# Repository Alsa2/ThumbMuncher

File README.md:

Stuff to add
- Perfect 1d engine model to gui
- PID I rate loss tunning

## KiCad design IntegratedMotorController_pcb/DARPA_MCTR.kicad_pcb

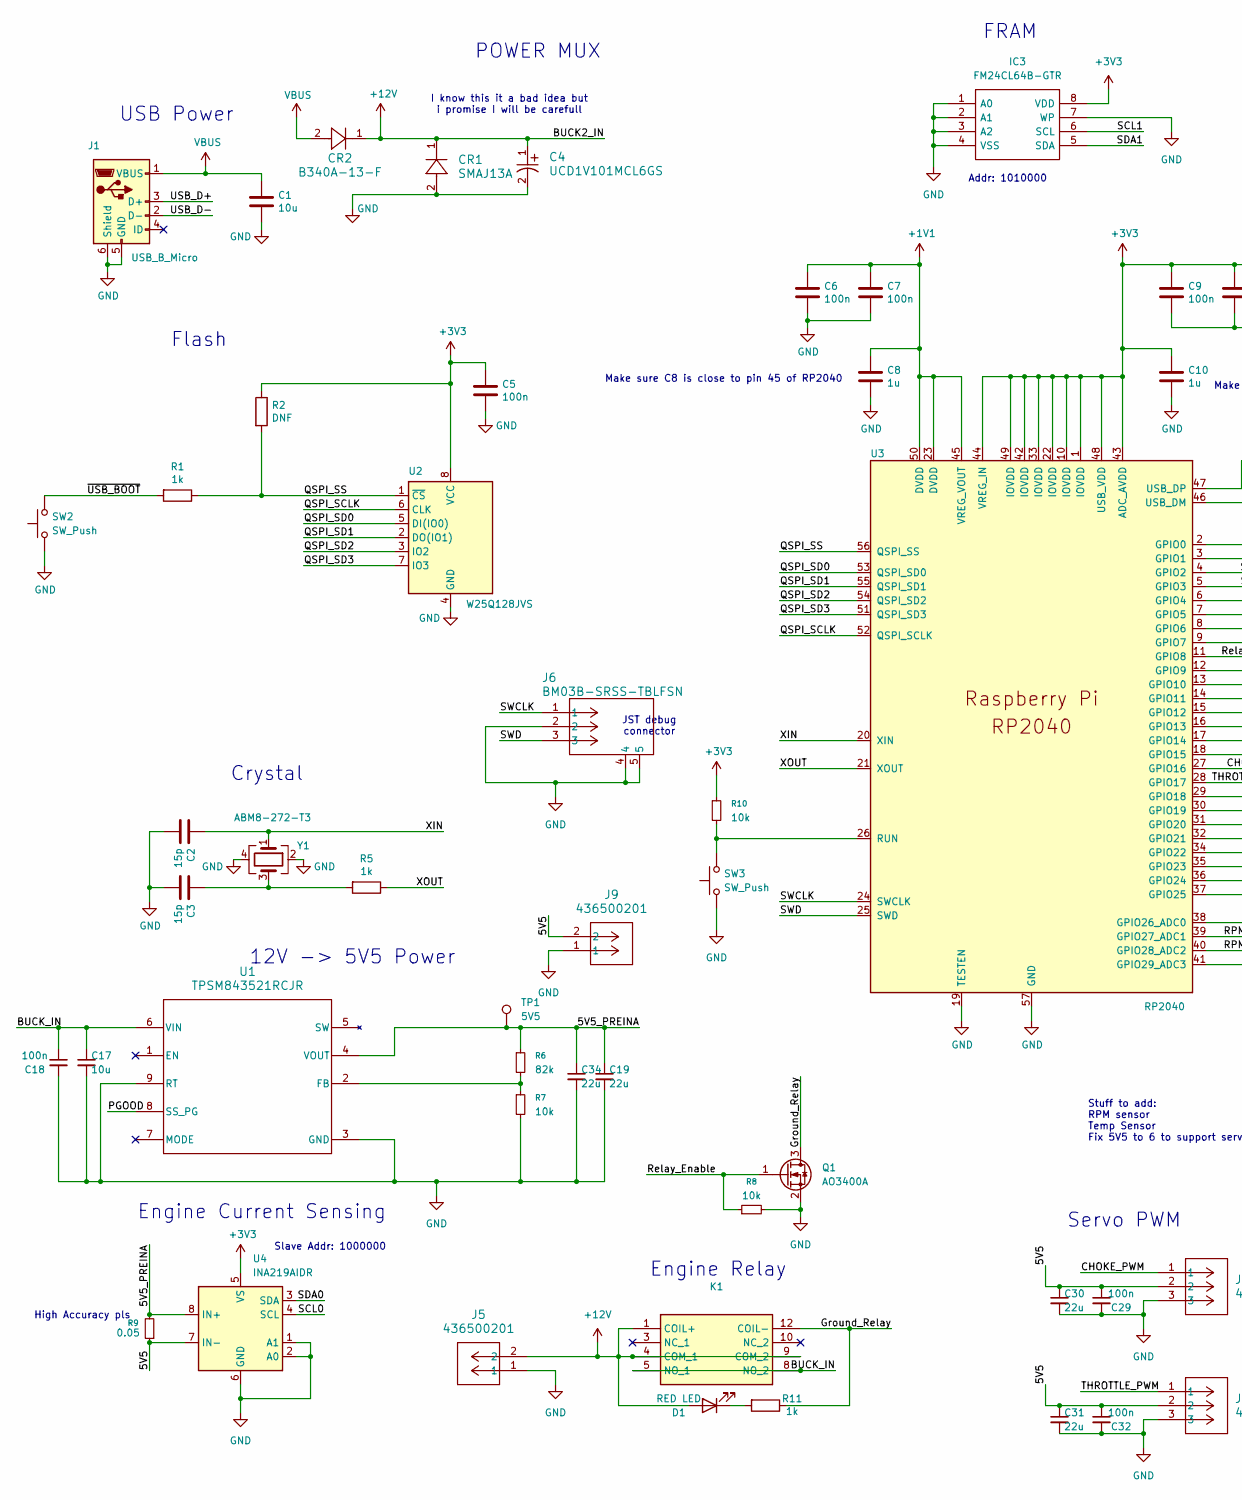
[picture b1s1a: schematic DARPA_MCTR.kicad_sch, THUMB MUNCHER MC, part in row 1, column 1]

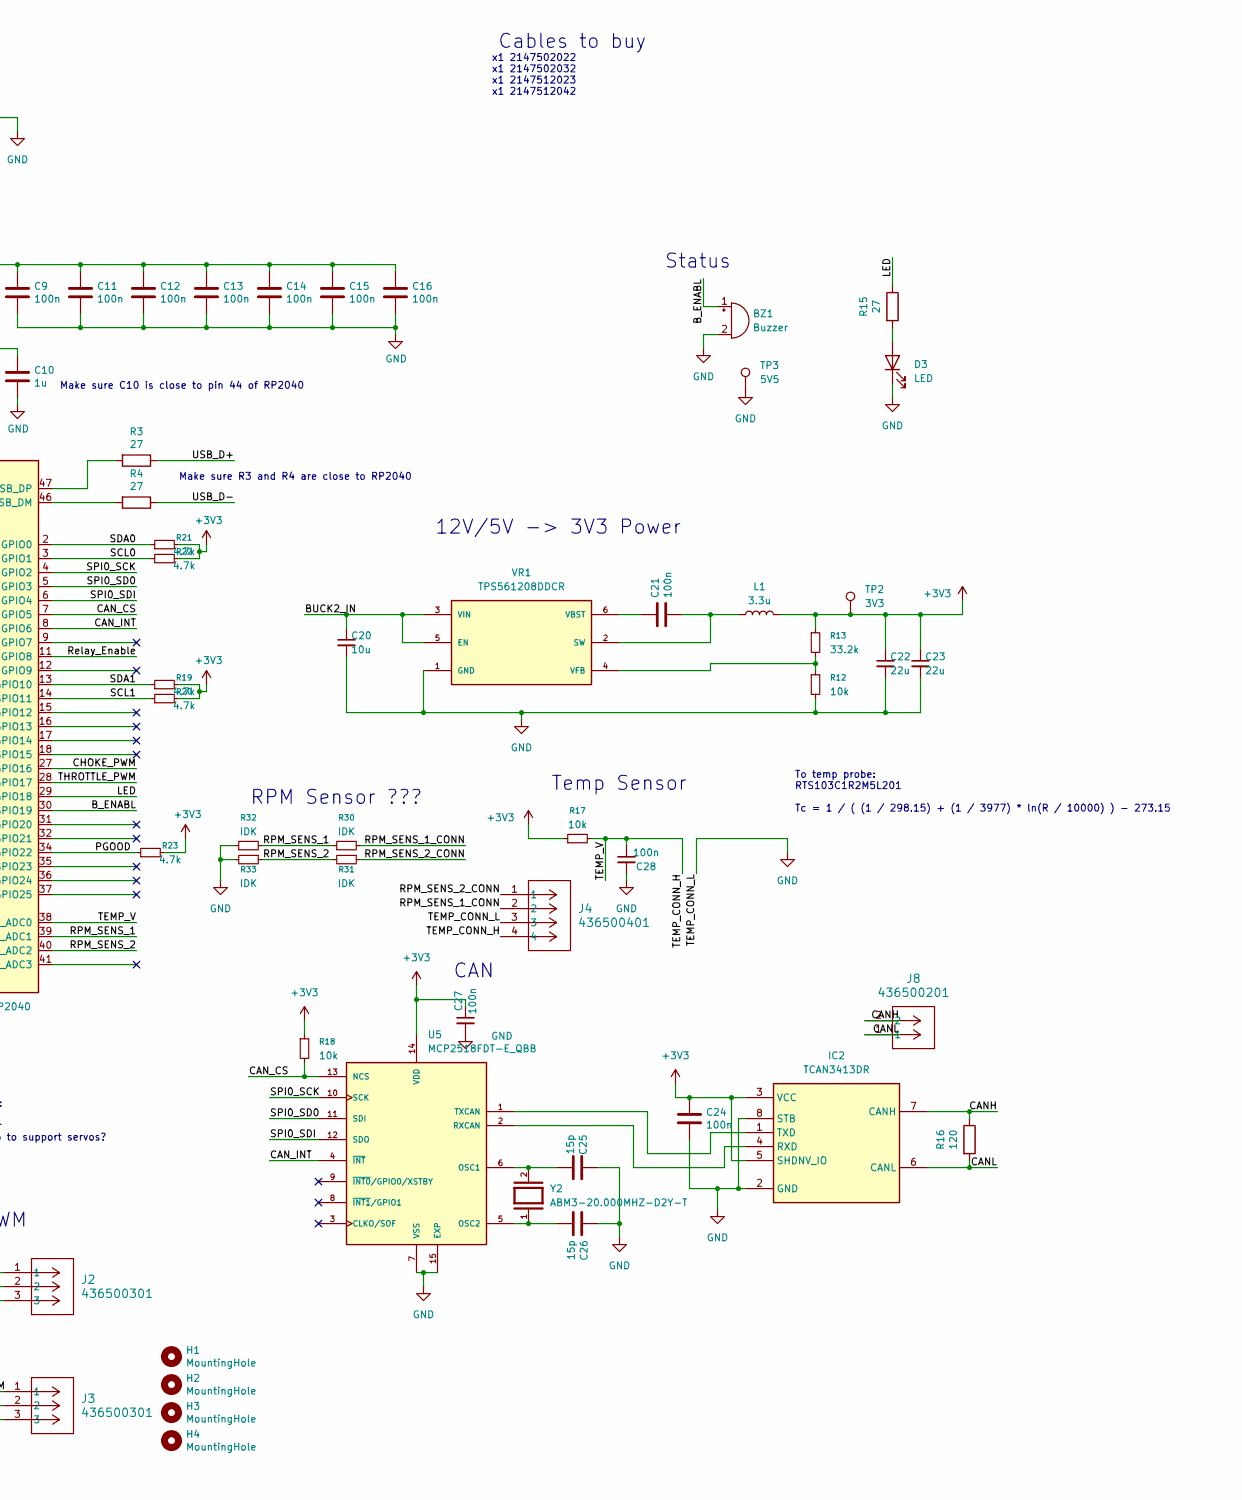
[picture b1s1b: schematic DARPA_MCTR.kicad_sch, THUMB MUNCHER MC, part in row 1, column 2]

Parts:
BZ1: Buzzer; XDCR_SMTB-1240-S-R; MPN SMTB-1240-S-R
C1, C17, C20: 10u; C_0805_2012Metric; MPN GRM21BR61C106KE15L; JLC C440198
C2, C3, C25, C26: 15p; C_0402_1005Metric; MPN GRM1555C1H150JA01D; JLC C1548
C4: UCD1V101MCL6GS; PCAP_6.3x7.7-ELECT_NCA; MPN UCD1V101MCL6GS; JLC C134220
C5, C6, C7, C9, C11, C12, C13, C14, C15, C16, C18, C21, C24, C27, C28, C29, C32: 100n; C_0402_1005Metric; MPN GRM155R71C104KA88D; JLC C71629
C8, C10: 1u; C_0402_1005Metric; MPN CL05A105KP5NNNC; JLC C14445
C19, C22, C23, C30, C31, C34: 22u; C_0805_2012Metric; MPN GRM21BR61A226ME44L; JLC C441864
CR1: SMAJ13A; SMASeries_LTF; MPN SMAJ13A; JLC C5356038
CR2: B340A-13-F; DIODE_SODB340_2P92X4P6_DIO; MPN B340A-13-F; JLC C85098
D1: RED LED; LED_0603_1608Metric; MPN QBLP601-S3; JLC C9900174479
D3: LED; LED_0603_1608Metric; MPN 150060GS75020; JLC C9900202211
H1, H2, H3, H4: MountingHole; MountingHole_2.7mm_M2.5
IC2: TCAN3413DR; SOIC127P602X173-8N; Manufacturer_Part_Number TCAN3413DR; Mouser Part Number 595-TCAN3413DR
IC3: FM24CL64B-GTR; SOIC127P602X173-8N; Manufacturer_Part_Number FM24CL64B-GTR; Mouser Part Number 877-FM24CL64B-GTR
J1: USB_B_Micro; USB_Micro-B_Amphenol_10103594-0001LF_Horizontal_modified; MPN 10103594-0001LF; JLC C428495
J2, J3: 436500301; CONN_SD-43650-001_03_MOL; MPN 0436500301
J4: 436500401; CONN_SD-43650-001_04_MOL; MPN 0436500401
J5, J8, J9: 436500201; CONN_SD-43650-001_02_MOL; MPN 0436500201
J6: BM03B-SRSS-TBLFSN; CONN_BM03B-SRSS-TBLFSN_JST; JLC C160389
K1: TX2-12V-TH; TX212VTH; Manufacturer_Part_Number TX2-12V-TH; Mouser Part Number 769-TX2-12V-TH
L1: 3.3u; IND_BOURNS_SDR0403; MPN SDR0403-3R3ML; JLC C139481
Q1: AO3400A; SOT-23-3; MPN AO3400A; JLC C20917
R1, R5, R11: 1k; R_0402_1005Metric; MPN RC0402FR-071KL; JLC C11702
R2: DNF; R_0402_1005Metric
R3, R4, R15: 27; R_0402_1005Metric; MPN RC0402FR-0727RL; JLC C25100
R6: 82k; R_0603_1608Metric; MPN RC0603FR-0782KL; JLC C23254
R7, R8, R10, R12, R17, R18: 10k; R_0603_1608Metric; MPN RC0603FR-0710KL; JLC C25804
R9: 0.05; R_2512_6332Metric; MPN WSL2512R0500FEA; JLC C413486
R13: 33.2k; R_0603_1608Metric; MPN RC0603FR-0733K2L; JLC C4089611
R16: 120; R_0402_1005Metric; MPN RC0402FR-07120RL; JLC C23162
R19, R20, R21, R22, R23: 4.7k; R_0603_1608Metric; MPN RC0603FR-074K7L; JLC C23162
R30, R31, R32, R33: IDK; R_0603_1608Metric
SW2, SW3: SW_Push; SW_SPST_EVQP2_ShortPushTravel_H2.1mm; MPN EVQ-P2602W; JLC C79161
TP1, TP3: 5V5; TestPoint_Pad_1.0x1.0mm
TP2: 3V3; TestPoint_Pad_1.0x1.0mm
U1: TPSM843521RCJR; RCJ0009A-MFG; MPN TPSM843521RCJR; JLC C48581090
U2: W25Q128JVS; SOIC-8_5.3x5.3mm_P1.27mm; MPN W25Q128JVSIQ; JLC C97521
U3: RP2040; RP2040-QFN-56; MPN SC0914(13); JLC C2040
U4: INA219AIDR; SOIC-8_3.9x4.9mm_P1.27mm; MPN INA219AIDR; JLC C138706
U5: MCP2518FDT-E_QBB; DFN-14-1EP_3x4.5mm_P0.65mm_EP1.65x4.25mm; PARTREV B; DigiKey_Part_Number MCP2518FDT-E/QBBCT-ND
VR1: TPS561208DDCR; SOT95P280X110-6N; PARTREV April 2017; DigiKey_Part_Number 296-47886-1-ND
Y1: ABM8-272-T3; Crystal_SMD_3225-4Pin_3.2x2.5mm; MPN ABM8-272-T3; JLC C20625731
Y2: ABM3-20.000MHZ-D2Y-T; XTAL_ABM3-20.000MHZ-D2Y-T; PARTREV 4/25/2022; DigiKey_Part_Number 535-10641-1-ND

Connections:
+1V1: C6.1, C7.1, C8.1, U3.23 (DVDD), U3.45 (VREG_VOUT), U3.50 (DVDD)
+3V3: C5.1, C9.1, C10.1, C11.1, C12.1, C13.1, C14.1, C15.1, C16.1, C22.1, C23.1, C24.1, C27.1, IC2.3 (VCC), IC2.5 (SHDNV_IO), IC3.8 (VDD), L1.2, R2.1, R10.1, R13.1, R17.1, R18.1, R19.2, R20.2, R21.2, R22.2, R23.2, TP2.1 (1_1), U2.8 (VCC), U3.1 (IOVDD), U3.10 (IOVDD), U3.22 (IOVDD), U3.33 (IOVDD), U3.42 (IOVDD), U3.43 (ADC_AVDD), U3.44 (VREG_IN), U3.48 (USB_VDD), U3.49 (IOVDD), U4.5 (VS), U5.14 (VDD)
+12V: C4.1, C20.1, CR1.1, CR2.1, D1.2 (A), J5.2, K1.1 (COIL+), K1.4 (COM_1), K1.9 (COM_2), VR1.3 (VIN), VR1.5 (EN)
/5V5: C29.1, C30.1, C31.1, C32.1, J2.2, J3.2, J9.2, R9.1, U4.7 (IN-)
/5V5_PREINA: C19.1, C34.1, R6.1, R9.2, TP1.1 (1_1), U1.4 (VOUT), U4.8 (IN+)
/BUCK_IN: C17.1, C18.1, K1.5 (NO_1), K1.8 (NO_2), U1.6 (VIN)
/B_ENABL: BZ1.1 (+), U3.30 (GPIO19)
/CANH: IC2.7 (CANH), J8.2, R16.1
/CANL: IC2.6 (CANL), J8.1, R16.2
/CAN_CS: R18.2, U3.7 (GPIO5), U5.13 (NCS)
/CAN_INT: U3.8 (GPIO6), U5.4 (~INT)
/CHOKE_PWM: J2.1, U3.27 (GPIO16)
/Ground_Relay: K1.12 (COIL-), Q1.3 (D), R11.1
/LED: R15.1, U3.29 (GPIO18)
/PGOOD: R23.1, U1.8 (SS_PG), U3.34 (GPIO22)
/QSPI_SCLK: U2.6 (CLK), U3.52 (QSPI_SCLK)
/QSPI_SD0: U2.5 (DI(IO0)), U3.53 (QSPI_SD0)
/QSPI_SD1: U2.2 (DO(IO1)), U3.55 (QSPI_SD1)
/QSPI_SD2: U2.3 (IO2), U3.54 (QSPI_SD2)
/QSPI_SD3: U2.7 (IO3), U3.51 (QSPI_SD3)
/QSPI_SS: R1.1, R2.2, U2.1 (~CS), U3.56 (QSPI_SS)
/RPM_SENS_1: R30.1, R32.2, U3.39 (GPIO27_ADC1)
/RPM_SENS_1_CONN: J4.2, R30.2
/RPM_SENS_2: R31.2, R33.1, U3.40 (GPIO28_ADC2)
/RPM_SENS_2_CONN: J4.1, R31.1
/Relay_Enable: Q1.1 (G), R8.1, U3.11 (GPIO8)
/SCL0: R22.1, U3.3 (GPIO1), U4.4 (SCL)
/SCL1: IC3.6 (SCL), R20.1, U3.14 (GPIO11)
/SDA0: R21.1, U3.2 (GPIO0), U4.3 (SDA)
/SDA1: IC3.5 (SDA), R19.1, U3.13 (GPIO10)
/SPI0_SCK: U3.4 (GPIO2), U5.10 (SCK)
/SPI0_SD0: U3.5 (GPIO3), U5.11 (SDI)
/SPI0_SDI: U3.6 (GPIO4), U5.12 (SDO)
/SWCLK: J6.1, U3.24 (SWCLK)
/SWD: J6.3, U3.25 (SWD)
/TEMP_CONN_H: C28.1, J4.4, R17.2, U3.38 (GPIO26_ADC0)
/THROTTLE_PWM: J3.1, U3.28 (GPIO17)
/USB_D+: J1.3 (D+), R3.1
/USB_D-: J1.2 (D-), R4.1
/XIN: C2.1, U3.20 (XIN), Y1.1
/XOUT: R5.1, U3.21 (XOUT)
/~USB_BOOT: R1.2, SW2.2
GND: BZ1.2 (-), C1.2, C2.2, C3.2, C4.2, C5.2, C6.2, C7.2, C8.2, C9.2, C10.2, C11.2, C12.2, C13.2, C14.2, C15.2, C16.2, C17.2, C18.2, C19.2, C20.2, C22.2, C23.2, C24.2, C25.1, C26.1, C27.2, C28.2, C29.2, C30.2, C31.2, C32.2, C34.2, CR1.2, D3.1 (K), IC2.2 (GND), IC2.8 (STB), IC3.1 (A0), IC3.2 (A1), IC3.3 (A2), IC3.4 (VSS), IC3.7 (WP), J1.5 (GND), J1.6 (Shield), J2.3, J3.3, J4.3, J5.1, J6.2, J6.4, J6.5, J9.1, Q1.2 (S), R7.2, R8.2, R12.2, R32.1, R33.2, SW2.1, SW3.1, TP3.1, U1.3 (GND), U1.9 (RT), U2.4 (GND), U3.19 (TESTEN), U3.57 (GND), U4.1 (A1), U4.2 (A0), U4.6 (GND), U5.7 (VSS), U5.15 (EXP), VR1.1 (GND), Y1.2, Y1.4; also elsewhere on the board
unnamed: C3.1, R5.2, Y1.3
unnamed: D1.1 (K), R11.2
unnamed: D3.2 (A), R15.2
unnamed: IC2.4 (RXD), U5.2 (RXCAN)
unnamed: IC2.1 (TXD), U5.1 (TXCAN)
unnamed: R6.2, R7.1, U1.2 (FB)
unnamed: R10.2, SW3.2, U3.26 (RUN)
unnamed: R4.2, U3.46 (USB_DM)
unnamed: R3.2, U3.47 (USB_DP)
unnamed: C25.2, U5.6 (OSC1), Y2.2
unnamed: C26.2, U5.5 (OSC2), Y2.1
unnamed: C21.2, L1.1, VR1.2 (SW)
unnamed: C21.1, VR1.6 (VBST)
unnamed: R12.1, R13.2, VR1.4 (VFB)
VBUS: C1.1, CR2.2, J1.1 (VBUS)

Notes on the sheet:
12V -> 5V5 Power
Addr: 1010000
USB Power
High Accuracy pls
Crystal
I know this it a bad idea but i promise I will be carefull
CAN
Make sure C8 is close to pin 45 of RP2040
Slave Addr: 1000000
Cables to buy
Servo PWM
RPM Sensor ???
To temp probe: RTS103C1R2M5L201 Tc = 1 / ( (1 / 298.15) + (1 / 3977) * ln(R / 10000) ) - 273.15
POWER MUX
JST debug connector
Make sure C10 is close to pin 44 of RP2040
Stuff to add: RPM sensor Temp Sensor Fix 5V5 to 6 to support servos?
FRAM
Status
Engine Current Sensing
Make sure R3 and R4 are close to RP2040
Engine Relay
x1 2147502022 x1 2147502032 x1 2147512023 x1 2147512042
Temp Sensor
12V/5V -> 3V3 Power
Flash

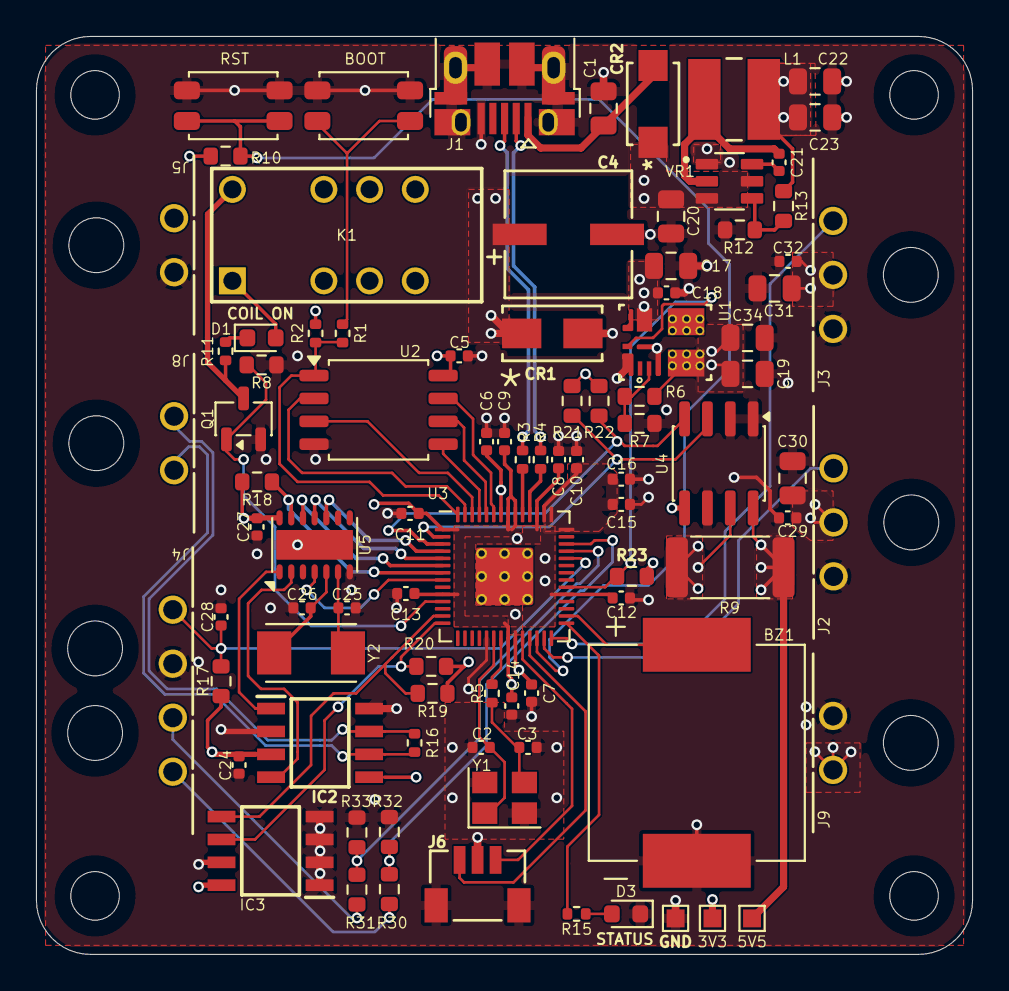
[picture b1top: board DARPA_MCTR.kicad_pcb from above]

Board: 4 copper layers, 52.0 x 51.0 mm, 94 parts (0 on the bottom side), 58 nets.

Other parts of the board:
GND: 5V5; TestPoint_Pad_1.0x1.0mm

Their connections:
GND: GND.1 (1_1); also elsewhere on the board

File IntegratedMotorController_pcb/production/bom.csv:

Designator,Footprint,Quantity,Value,LCSC Part #
BZ1,XDCR_SMTB-1240-S-R,1,Buzzer,SMTB-1240-S-R
"C1, C17, C20",0805,3,10u,GRM21BR61C106KE15L
"C10, C8",0402,2,1u,CL05A105KP5NNNC
"C11, C12, C13, C14, C15, C16, C18, C21, C24, C27, C28, C29, C32, C5, C6, C7, C9",0402,17,100n,GRM155R71C104KA88D
"C19, C22, C23, C30, C31, C34",0805,6,22u,GRM21BR61A226ME44L
"C2, C25, C26, C3",0402,4,15p,GRM1555C1H150JA01D
C4,PCAP_6.3x7.7-ELECT_NCA,1,UCD1V101MCL6GS,UCD1V101MCL6GS
CR1,SMASeries_LTF,1,SMAJ13A,SMAJ13A
CR2,DIODE_SODB340_2P92X4P6_DIO,1,B340A-13-F,B340A-13-F
D1,0603,1,RED LED,QBLP601-S3
D3,0603,1,LED,150060GS75020
IC2,SOIC127P602X173-8N,1,TCAN3413DR,TCAN3413DR
IC3,SOIC127P602X173-8N,1,FM24CL64B-GTR,FM24CL64B-GTR
J1,USB_Micro-B_Amphenol_10103594-0001LF_Horizontal_modified,1,USB_B_Micro,10103594-0001LF
"J2, J3",CONN_SD-43650-001_03_MOL,2,436500301,0436500301
J4,CONN_SD-43650-001_04_MOL,1,436500401,0436500401
"J5, J8, J9",CONN_SD-43650-001_02_MOL,3,436500201,0436500201
J6,CONN_BM03B-SRSS-TBLFSN_JST,1,BM03B-SRSS-TBLFSN,
K1,TX212VTH,1,TX2-12V-TH,TX2-12V-TH
L1,IND_BOURNS_SDR0403,1,3.3u,SDR0403-3R3ML
Q1,SOT-23-3,1,AO3400A,AO3400A
"R1, R11, R5",0402,3,1k,RC0402FR-071KL
"R10, R12, R17, R18, R7, R8",0603,6,10k,RC0603FR-0710KL
R13,0603,1,33.2k,RC0603FR-0733K2L
"R15, R3, R4",0402,3,27,RC0402FR-0727RL
R16,0402,1,120,RC0402FR-07120RL
"R19, R20, R21, R22, R23",0603,5,4.7k,RC0603FR-074K7L
R6,0603,1,82k,RC0603FR-0782KL
R9,2512,1,0.05,WSL2512R0500FEA
"SW2, SW3",SW_SPST_EVQP2_ShortPushTravel_H2.1mm,2,SW_Push,EVQ-P2602W
U1,RCJ0009A-MFG,1,TPSM843521RCJR,TPSM843521RCJR
U2,SOIC-8_5.3x5.3mm_P1.27mm,1,W25Q128JVS,W25Q128JVSIQ
U3,RP2040-QFN-56,1,RP2040,SC0914(13)
U4,SOIC-8_3.9x4.9mm_P1.27mm,1,INA219AIDR,INA219AIDR
U5,DFN-14-1EP_3x4.5mm_P0.65mm_EP1.65x4.25mm,1,MCP2518FDT-E_QBB,MCP2518FDT-E/QBB
VR1,SOT95P280X110-6N,1,TPS561208DDCR,TPS561208DDCR
Y1,Crystal_SMD_3225-4Pin_3.2x2.5mm,1,ABM8-272-T3,ABM8-272-T3
Y2,XTAL_ABM3-20.000MHZ-D2Y-T,1,ABM3-20.000MHZ-D2Y-T,ABM3-20.000MHZ-D2Y-T

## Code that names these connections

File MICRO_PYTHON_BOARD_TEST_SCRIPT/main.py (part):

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PIN_SDA0 = 0
PIN_SCL0 = 1

PIN_SPI0_SCK = 2
PIN_SPI0_MOSI = 3
PIN_SPI0_MISO = 4
PIN_CAN_CS = 5
PIN_CAN_INT = 6

PIN_RELAY_EN = 8

PIN_SDA1 = 10
PIN_SCL1 = 11

PIN_CHOKE_PWM = 16
PIN_THROTTLE_PWM = 17

PIN_LED = 18
PIN_BUZZER = 19

PIN_PGOOD = 21
PIN_POWER_SRC = 23

PIN_TEMP_ADC = 26
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        phase=0,
        bits=8,
        firstbit=SPI.MSB,
        sck=Pin(PIN_SPI0_SCK),
        mosi=Pin(PIN_SPI0_MOSI),
        miso=Pin(PIN_SPI0_MISO),
    )

    mcp = MCP2518FD(spi, PIN_CAN_CS, PIN_CAN_INT)

    diag = mcp.read_diagnostics()
    print_mcp_diag(diag)
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        banner("STATUS INPUTS")

        try:
            pgood = Pin(PIN_PGOOD, Pin.IN).value()
            src = Pin(PIN_POWER_SRC, Pin.IN).value()
            can_int = Pin(PIN_CAN_INT, Pin.IN, Pin.PULL_UP).value()

            record(
                "PGOOD GP21",
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            print("  Sampling RPM analog inputs for 1 second.")
            print("  Spin the source now if applicable.")

            v1 = sample_adc(PIN_RPM1_ADC, "RPM_SENS_1 / GP27")
            v2 = sample_adc(PIN_RPM2_ADC, "RPM_SENS_2 / GP28")

            record(
                "RPM_SENS_1 GP27",
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
    if ENABLE_PWM_OUTPUT_TESTS:
        print("  Running PWM output tests.")
        test_pwm_output(PIN_CHOKE_PWM, "CHOKE_PWM GP16")
        test_pwm_output(PIN_THROTTLE_PWM, "THROTTLE_PWM GP17")
    else:
        print("  PWM output tests skipped.")

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
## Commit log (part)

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2026-05-13 Added Readme
2026-06-07 new version 1.1
2026-06-30 Some cleanup and new stuff
